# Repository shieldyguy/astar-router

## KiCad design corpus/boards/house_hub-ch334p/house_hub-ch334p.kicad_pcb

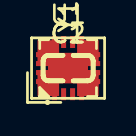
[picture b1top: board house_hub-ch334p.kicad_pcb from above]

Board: 2 copper layers, 4 parts (0 on the bottom side), 5 nets, no tracks yet.

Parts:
C1, C2: 1uF; CL10A105KB8NNNC
U1: CH334P
Y1: 12MHz; X322512MSB4SI

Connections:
GND: C1.2, C2.2, U1.17 (GND), Y1.2, Y1.4
unnamed: C2.1, U1.16 (VDD33)
unnamed: U1.2 (XI), Y1.1
unnamed: U1.1 (XO), Y1.3
VBUS: C1.1, U1.15 (V5)

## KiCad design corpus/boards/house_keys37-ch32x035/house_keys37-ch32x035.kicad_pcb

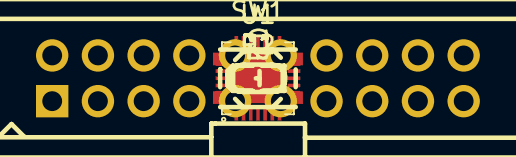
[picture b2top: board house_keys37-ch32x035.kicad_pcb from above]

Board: 2 copper layers, 8 parts (0 on the bottom side), 24 nets, no tracks yet.

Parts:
C1: 100nF; CC0603KRX7R9BB104
C2: 10uF; CL10A106KP8NNNC
D1: KEYS; KT-0603R
J1: KEY37; 2.54-2*10P
R1: 5.1kΩ; 0603WAF5101T5E
R2: 1kΩ; 0603WAF1001T5E
SW1: BOOT; GT-TC048D-H025-L1
U1: CH32X035G8U6

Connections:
+3V3: C1.1, C2.1, SW1.3, U1.2 (VDD)
BR4: J1.1, U1.10 (PA5/SCK/TX4_/O2N0/A5)
BR5: J1.5, U1.14 (PB3/TX3/T2C3_/T2C3N_/O2P1)
BR6: J1.9, U1.17 (PB6/T1C1N/CTS3/O1N1)
BR7: J1.13, U1.20 (PB9/T1C1/MCO/TX4_)
BR8: J1.17, U1.25 (PC18/DIO/TX3_/T2C1N_/T3C2_/I2C_/T1ET_)
GND: C1.2, C2.2, D1.2, U1.29 (GND)
MK4: J1.3, U1.12 (PA7/MOSI/T3C2/T1C1N_/TX1_/O2P0/A7)
MK5: J1.7, U1.15 (PB4/T2C4_/T3C1_/T2BK_/RX3/O1P2)
MK6: J1.11, U1.18 (PB7/T1C2N/RTS3_/O2P2)
MK7: J1.15, U1.23 (PB12/T1C4_/T2C2N_)
MK8: J1.19, U1.28 (PC14/CC1/T1C3_/T2C2_)
unnamed: D1.1, R2.2
unnamed: R1.2, SW1.1
unnamed: R2.1, U1.1 (PC15/CC2/T2C3_/T1ET_)
SCAN0: J1.2, U1.9 (PA4/CS/O2O0/T3C2_/A4)
SCAN1: J1.4, U1.11 (PA6/MISO/T3C1/T1BK_/O1N0/A6)
SCAN2: J1.6, U1.13 (PB0/TX4/T1C2N_/O1P0/A8)
SCAN3: J1.8, U1.6 (PA1/RTS2/T2C2/C1O/O1N2/O2N2/A1)
SCAN4: J1.10, U1.16 (PB1/T1C3N_/RX4/O2N1/A9/PB5/O1O1/T3C2_/T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)
SCAN5: J1.12, U1.19 (PB8/T1C3N/O1P1)
SCAN6: J1.14, U1.3 (PC0/TX2_/T2C4_/T1C1_/T2BK_/A10)
SCAN7: J1.16, U1.24 (PC19/DCK/T2C1_/T3C1_/I2C_/RX3_/C1P0)
USB_DP: R1.1, U1.27 (PC17/UDP/RTS1/TX4_/I2C_/RX4_/T1ET/PC10)

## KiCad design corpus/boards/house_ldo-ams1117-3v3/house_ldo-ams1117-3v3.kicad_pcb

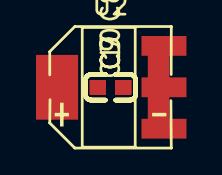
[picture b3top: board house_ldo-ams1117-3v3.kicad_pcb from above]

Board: 2 copper layers, 5 parts (0 on the bottom side), 3 nets, no tracks yet.

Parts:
C7, C10: 100nF; CC0603KRX7R9BB104
C8: 220uF; RVT220UF16V67RV0015
C9: 10uF; CL10A106KP8NNNC
U2: AMS1117-3.3

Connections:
+3V3: C8.1, C9.1, C10.1, U2.2, U2.4
+5V: C7.1, U2.3
GND: C7.2, C8.2, C9.2, C10.2, U2.1

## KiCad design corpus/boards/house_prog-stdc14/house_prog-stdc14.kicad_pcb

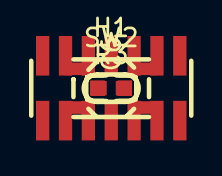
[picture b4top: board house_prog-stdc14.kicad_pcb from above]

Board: 2 copper layers, 4 parts (0 on the bottom side), 3 nets, no tracks yet.

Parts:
C6: 100nF; CC0603KRX7R9BB104
H1: STDC14; PZ127-2-07-S
R3: 10kΩ; 0603WAF1002T5E
SW2: RST; GT-TC048D-H025-L1

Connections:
+3V3: H1.3, R3.2
GND: C6.2, H1.5, H1.7, H1.11, SW2.3
NRST: C6.1, H1.12, R3.1, SW2.1

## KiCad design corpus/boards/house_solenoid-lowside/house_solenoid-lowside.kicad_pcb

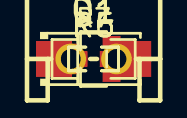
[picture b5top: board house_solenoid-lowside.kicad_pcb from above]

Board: 2 copper layers, 6 parts (0 on the bottom side), 5 nets, no tracks yet.

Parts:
D1: SS34
J3: SOLENOID; S2B-XH-A(LF)(SN)
Q1: AO3400A
R5: 100Ω; 0603WAF1000T5E
R6: 10kΩ; 0603WAF1002T5E
R7: 100mΩ; 1206W4F100LT5E

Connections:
+24V: D1.1, J3.1
GND: R6.2, R7.2
ISENSE: Q1.2, R7.1
unnamed: D1.2, J3.2, Q1.3
unnamed: Q1.1, R5.2, R6.1

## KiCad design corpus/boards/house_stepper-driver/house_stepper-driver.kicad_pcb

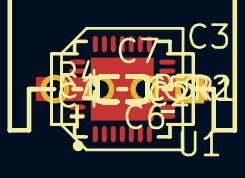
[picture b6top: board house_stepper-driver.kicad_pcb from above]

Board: 2 copper layers, 13 parts (0 on the bottom side), 15 nets, no tracks yet.

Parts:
C1, C2, C4, C7: 100nF; CC0603KRX7R9BB104
C3: 100uF; RVT1H101M0607
C5: 22nF; CL10B223KB8NNNC
C6: 2.2uF; CL10A225KA8NNNC
J1: STEPPER; S4B-XH-A(LF)(SN)
R1, R2: 110mΩ; FRL2512FR110TS
R3: 1kΩ; 0603WAF1001T5E
R4: 10kΩ; 0603WAF1002T5E
U1: TMC2209; TMC2209-LA-T

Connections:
+3V3: C7.1, R4.1, U1.15
+24V: C1.1, C2.1, C3.1, C4.1, U1.22, U1.28
A1: J1.1, U1.24
A2: J1.2, U1.21
B1: J1.3, U1.26
B2: J1.4, U1.1
ENN: R4.2, U1.2
GND: C1.2, C2.2, C3.2, C6.2, C7.2, R1.2, R2.2, U1.3, U1.7, U1.9, U1.10, U1.13, U1.17, U1.18, U1.20, U1.25, U1.29
unnamed: C6.1, U1.8
unnamed: R1.1, U1.23
unnamed: R2.1, U1.27
unnamed: C5.2, U1.5
unnamed: C5.1, U1.4
unnamed: C4.2, U1.6
UART_PDN: R3.1, U1.14

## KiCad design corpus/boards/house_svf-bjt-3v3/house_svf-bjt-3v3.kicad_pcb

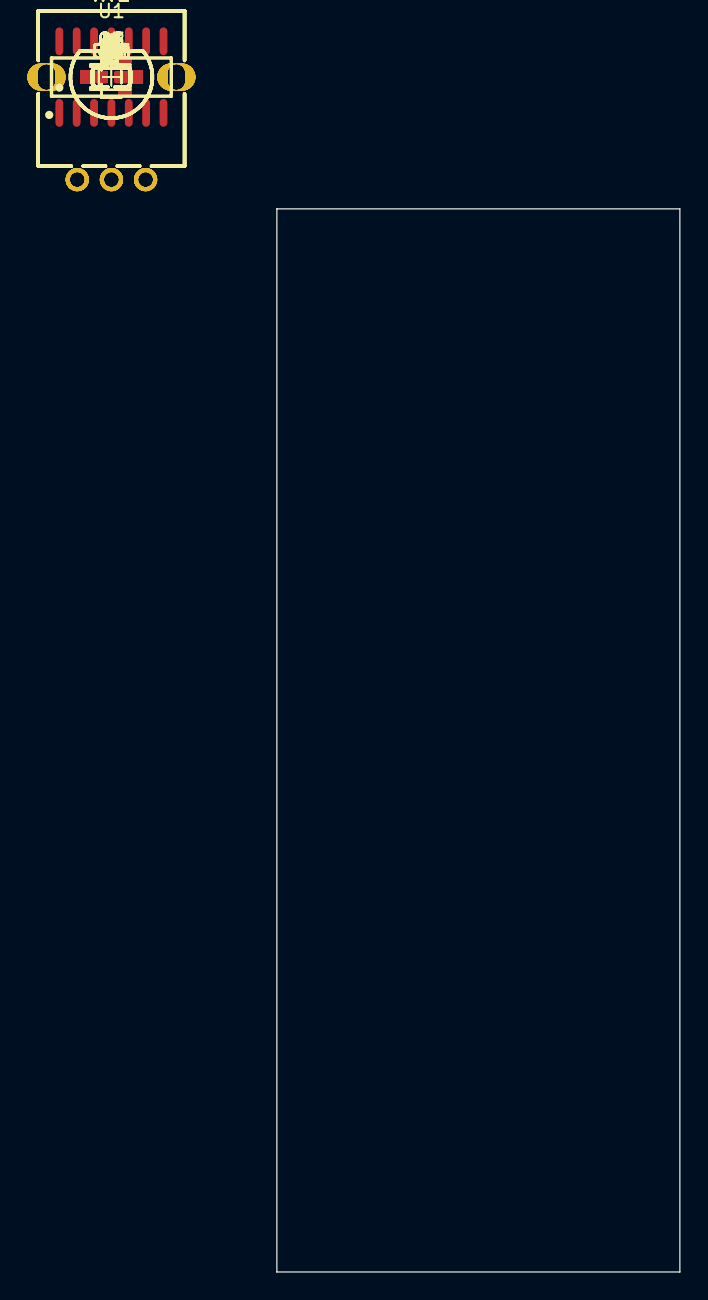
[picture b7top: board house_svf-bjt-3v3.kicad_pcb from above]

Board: 2 copper layers, 29.5 x 77.8 mm, 38 parts (0 on the bottom side), 21 nets, no tracks yet.

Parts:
C1, C9: 100nF; CC0603KRX7R9BB104
C4, C5, C12: 220pF; GCM1885C2A221JA16D
C6, C7, C8, C11: 10uF; CL10A106KP8NNNC
D1, D2: 1N4148W
Q1, Q2: MMBT3904(RANGE:100-300); MMBT3904(RANGE_100-300)
Q3: MMBT3906
R1, R2, R3, R4, R6, R10, R18: 10kΩ; 0603WAF1002T5E
R5: 8.2kΩ; 0603WAF8201T5E
R7: 180kΩ; 0603WAF1803T5E
R9: 51kΩ; 0603WAF5102T5E
R11: 100Ω; 0603WAF1000T5E
R13: 33kΩ; 0603WAF3302T5E
R14: 1kΩ; 0603WAF1001T5E
R16, R17, R25: 100kΩ; 0603WAF1003T5E
R21, R22: 470Ω; 0603WAF4700T5E
R23, R24: 10Ω; 0603WAF100JT5E
RV1, RV2, RV3: 10kΩ; RK09L1140A2U
U1: MCP6004; MCP6004T-I_SL

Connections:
+3V3: C9.1, R4.1, R6.1, R10.1, R16.2, RV1.3, U1.4
GND: C1.1, C9.2, R5.2, R17.1, RV1.1, U1.11
LP: C5.1, C6.2, C12.1, R3.1, U1.8
unnamed: C1.2, R16.1, R17.2, U1.3
unnamed: C4.1, C7.2, D1.2, D2.1, R22.1, R25.1, RV2.1, U1.7
unnamed: C4.2, Q1.2, U1.6
unnamed: C5.2, Q2.2, U1.9
unnamed: C8.2, R1.1, R21.1, U1.14
unnamed: C11.1, R2.2
unnamed: C11.2, RV3.2
unnamed: D1.1, D2.2, R13.2, U1.12
unnamed: Q1.1, Q2.1, Q3.2, R4.2
unnamed: Q1.3, R21.2, R23.1
unnamed: Q2.3, R22.2, R24.1
unnamed: Q3.1, R5.1, R6.2, R7.2, R9.2
unnamed: Q3.3, R10.2, R11.1
unnamed: R9.1, RV1.2
unnamed: R13.1, R14.1, RV2.2
unnamed: R18.1, RV3.3
SUM: C12.2, R1.2, R2.1, R3.2, R25.2, U1.13
VREF: R11.2, R14.2, R23.2, R24.2, RV2.3, RV3.1, U1.1, U1.2, U1.5, U1.10

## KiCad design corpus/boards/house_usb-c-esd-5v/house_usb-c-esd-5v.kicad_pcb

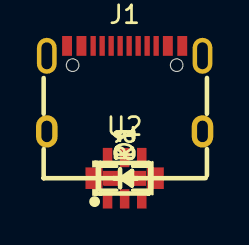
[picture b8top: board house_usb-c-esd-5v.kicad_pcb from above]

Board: 2 copper layers, 5 parts (0 on the bottom side), 6 nets, no tracks yet.

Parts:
D1: B5819W SL; B5819W_SL
J1: USB-C; TYPE-C_16PIN_2MD(073)
R1, R2: 5.1kΩ; 0603WAF5101T5E
U2: USBLC6-2SC6

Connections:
GND: J1.13 (EH), J1.14 (EH), J1.A1B12 (GND), J1.B1A12 (GND), R1.2, R2.2, U2.2
unnamed: J1.A5 (CC1), R1.1
unnamed: J1.B5 (CC2), R2.1
unnamed: J1.A7 (Dn1), J1.B7 (Dn2), U2.1
unnamed: J1.A6 (Dp1), J1.B6 (Dp2), U2.3
VBUS: D1.2, J1.A4B9 (VBUS), J1.B4A9 (VBUS), U2.5
